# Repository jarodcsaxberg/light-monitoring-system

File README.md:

# Light Monitoring System

This project seeks to design a light sensor that can be placed in the Hoosier National Forest for a prolonged period of time. The sensor will collect data on the light conditions during the night to obtain an official designation from the International Dark Sky Association (ISDA) for the Hoosier National Forest. The designation is important to attract more visitors to the Forest, to create community-involved programs regarding data collection from the sensors, and to teach people about what the IDSA association strives to do and why it is important.

## Project Code

The code can be found in [project/](https://github.com/jarodcsaxberg/light-monitoring-system/tree/master/project), with the custom written code found in [project/Inc](https://github.com/jarodcsaxberg/light-monitoring-system/tree/master/project/Inc) and [project/Src](https://github.com/jarodcsaxberg/light-monitoring-system/tree/master/project/Src).

## Design

The KiCad files for the PCB design can be found in [kicad_proj/e314_light_sensor](https://github.com/jarodcsaxberg/light-monitoring-system/tree/master/kicad_proj/e314_light_sensor).

A KiCad schematic is located [here](https://github.com/jarodcsaxberg/light-monitoring-system/blob/master/design_analysis/schematic.pdf).

The Fusion 360 files for the enclosure design can be found in [enclosure/](https://github.com/jarodcsaxberg/light-monitoring-system/tree/master/enclosure).

## Analysis

Cost and power analysis for the project is located in [cost_power_analysis/](https://github.com/jarodcsaxberg/light-monitoring-system/tree/master/cost_power_analysis).

Design analysis can be found in [design_analysis/](https://github.com/jarodcsaxberg/light-monitoring-system/tree/master/design_analysis).

## Final Report

The final report can be found in [final_report/](https://github.com/jarodcsaxberg/light-monitoring-system/tree/master/final_report).

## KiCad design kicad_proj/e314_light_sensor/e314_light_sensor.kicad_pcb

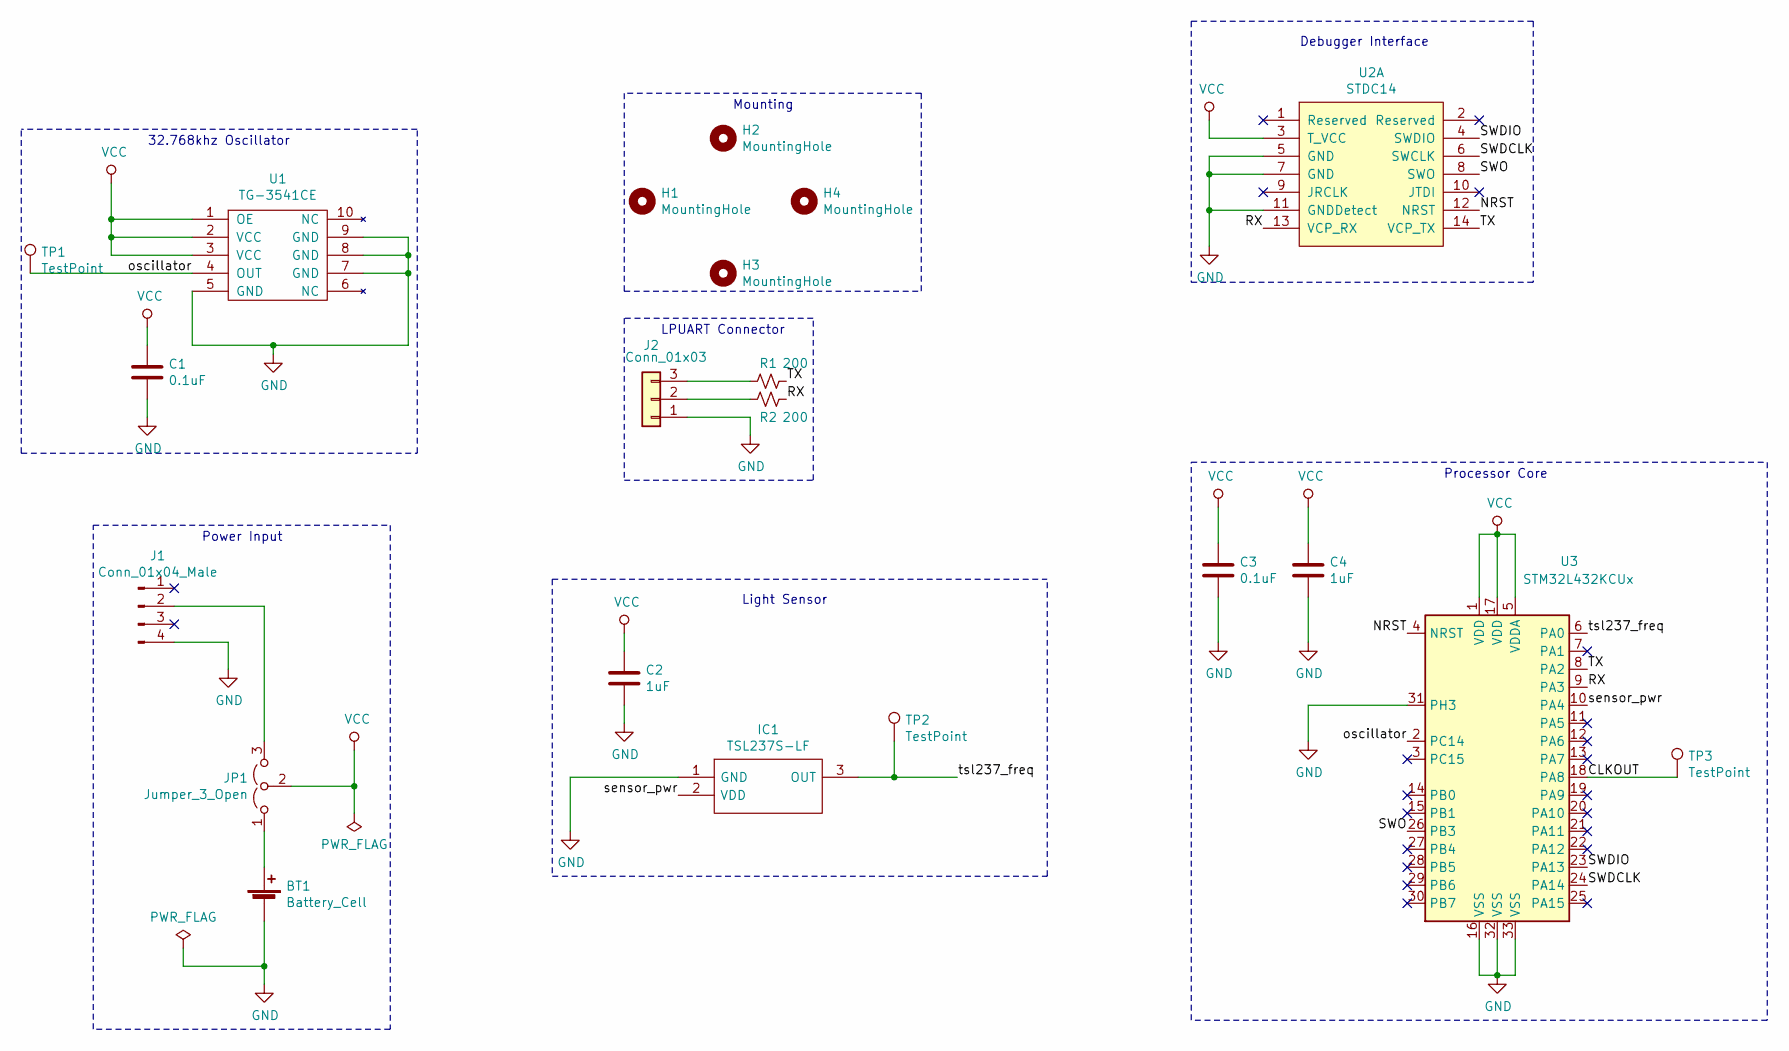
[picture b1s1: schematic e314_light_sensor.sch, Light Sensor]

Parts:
BT1: Battery_Cell; BatteryHolder_Keystone_1060_1x2032
C1, C3: 0.1uF; C_0603_1608Metric_Pad1.05x0.95mm_HandSolder
C2, C4: 1uF; C_0603_1608Metric_Pad1.05x0.95mm_HandSolder
H1, H2, H3, H4: MountingHole; MountingHole_2.2mm_M2_Pad_Via
IC1: TSL237S-LF; Mouser Part Number 856-TSL237S-LF
J1: Conn_01x04_Male; JST_XH_B4B-XH-AM_1x04_P2.50mm_Vertical
J2: Conn_01x03; JST_XH_B3B-XH-AM_1x03_P2.50mm_Vertical
JP1: Jumper_3_Open; SolderJumper-3_P1.3mm_Open_RoundedPad1.0x1.5mm
R1, R2: 200; R_0603_1608Metric_Pad1.05x0.95mm_HandSolder
TP1, TP2, TP3: TestPoint; TestPoint_Pad_D1.5mm
U1: TG-3541CE
U2: STDC14; ftsh_14p_connector
U3: STM32L432KCUx; QFN-32-1EP_5x5mm_P0.5mm_EP3.45x3.45mm

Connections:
/CLKOUT: TP3.1, U3.18 (PA8)
/NRST: U2.12 (NRST), U3.4 (NRST)
/RX: R2.1, U2.13 (VCP_RX), U3.9 (PA3)
/SWDCLK: U2.6 (SWCLK), U3.24 (PA14)
/SWDIO: U2.4 (SWDIO), U3.23 (PA13)
/SWO: U2.8 (SWO), U3.26 (PB3)
/TX: R1.1, U2.14 (VCP_TX), U3.8 (PA2)
/oscillator: TP1.1, U1.4 (OUT), U3.2 (PC14)
/sensor_pwr: IC1.2 (VDD), U3.10 (PA4)
/tsl237_freq: IC1.3 (OUT), TP2.1, U3.6 (PA0)
GND: BT1.2 (-), C1.2, C2.2, C3.2, C4.2, IC1.1 (GND), J1.4, J2.1, U1.5 (GND), U1.7 (GND), U1.8 (GND), U1.9 (GND), U2.5 (GND), U2.7 (GND), U2.11 (GNDDetect), U3.16 (VSS), U3.31 (PH3), U3.32 (VSS), U3.33 (VSS)
unnamed: BT1.1 (+), JP1.1 (A)
unnamed: J1.2, JP1.3 (B)
unnamed: J2.2, R2.2
unnamed: J2.3, R1.2
VCC: C1.1, C2.1, C3.1, C4.1, JP1.2 (C), U1.1 (OE), U1.2 (VCC), U1.3 (VCC), U2.3 (T_VCC), U3.1 (VDD), U3.5 (VDDA), U3.17 (VDD)

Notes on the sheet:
Debugger Interface
Processor Core
32.768khz Oscillator
Power Input
Light Sensor
LPUART Connector
Mounting

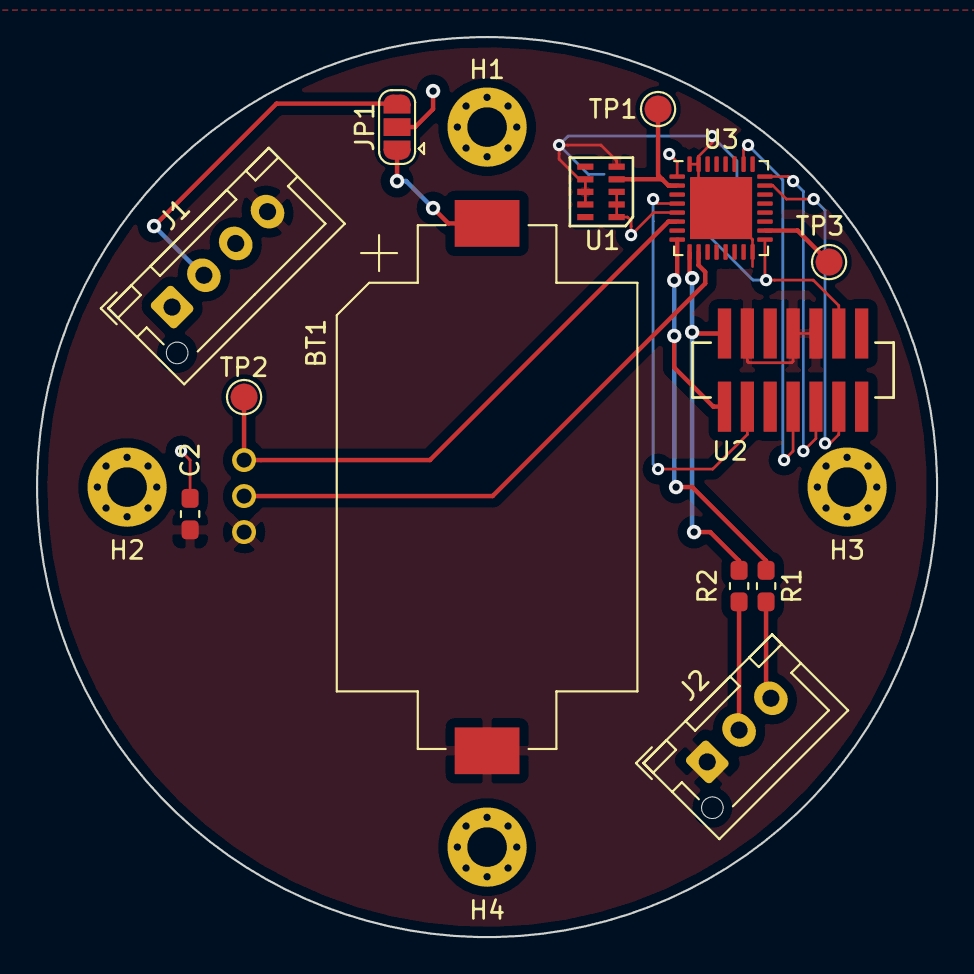
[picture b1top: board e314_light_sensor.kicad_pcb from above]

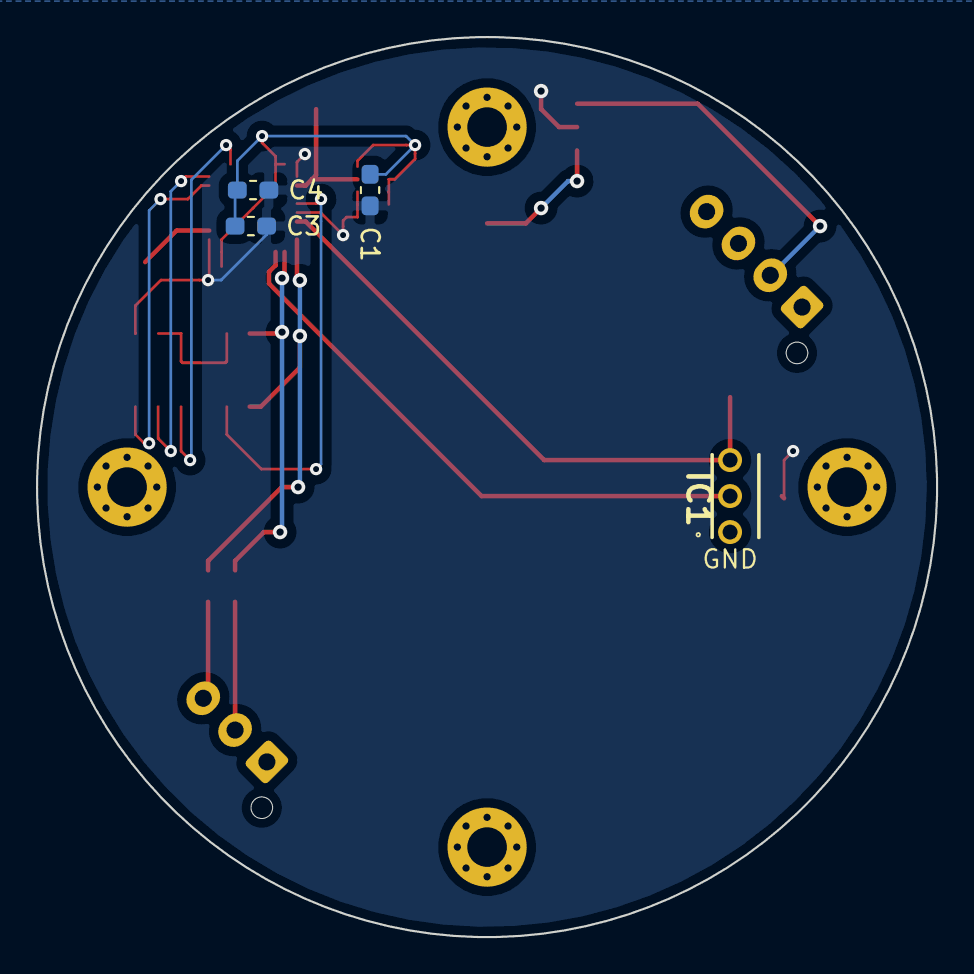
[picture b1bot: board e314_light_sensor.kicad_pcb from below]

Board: 2 copper layers, 50.0 x 50.0 mm, 21 parts (4 on the bottom side), 16 nets.

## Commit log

2020-07-10 Project upload
2020-07-10 Add links to readme
